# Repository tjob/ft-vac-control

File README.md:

# Use a Festool Bluetooth remote control with any vacuum

Use the Festool Bluetooth remote with vacuum extractors from other manufacturers.

The project contains the schematics and PCB layout designed using [KiCad 7](https://www.kicad.org/), and the firmware (written in C) for the [Raspberry Pi Pico](https://www.raspberrypi.com/products/raspberry-pi-pico/) to interface with a [Festool No. 202097 Bluetooth Remote Control add-on](https://www.amazon.co.uk/Festool-202097-Remote-Control-Blue/dp/B0794ZWFLR).

Festool sell an upgrade for their CT26/36/48 vacuum extractors to give remote control using Bluetooth, CT-F I/M-Set. It has two parts: the "CT-F I/M" installs in the extractor and the "CT-F I" is the button that attaches to the end of the vacuum hose. The button then starts and stops the extractor. Paired cordless tools with their Bluetooth-enabled batteries can also control the extractor.

But I don't have a CT26/36/48 extractor from Festool, so I wanted to create an adaptor that uses the module and controls a standard power socket to control any device attached. With a custom PCB, a Raspberry Pi Pico, some firmware, a Solid State Relay, and an enclosure I had a working solution.  Along the way I had to reverse-engineer the non-standard serial protocol and try to make sense of the bytes sent.

## Features
 - Allows connecting any vacuum extractor that has a physical switch capable of being always on. A vacuum with an NVR will not work.
 - Works with an unmodified Festool No. 202097 receiver. It's Plug and Play. At a later date if I ever get a CT extractor I wanted to be able to use this module again.
 - Has software safety features: automatically turns off if left on for an extended period. Uses the RP2040's hardware watchdog to shut off the power if the software stops for any reason.
 - Should work with Festool cordless tools with their Bluetooth batteries (untested). 

## How it works
The Festool module has three electrical connections to the host vacuum: two for power and one for data. The data line is serial, probably bidirectional, and uses a form of Manchester encoding. For more details on the serial stream and commands, see the [description of the traces](./software/traces/) captured with a logic analyzer.

The serial data from the receiver feeds the Raspberry Pi Pico via a BSS138 MOSFET as a level shifter. The Pico decodes the Manchester-encoded stream. When the Start/Stop commands are seen the software switches a Solid State Relay controlling mains AC supply to the output socket.

Wanting an excuse to learn KiCad, I designed a custom PCB to host the Pi Pico and a 4-pin 3.96 mm header to plug the CT-F I/M Bluetooth module into. The board contains a 240V switch-mode regulator providing 5V DC power to both the Pico and the CT-F I/M.

## :zap: Mains voltage electricity can kill! :zap: 

> [!WARNING] 
> This project description is not a guide and does not detail how to assemble a unit safely.  If you are not sure how to build one that is safe and complies with local laws and regulations, DO NOT ATTEMPT TO RECREATE.

## Bill of Materials

Parts on the PCB
| Part | Reference Designator | Description |
| ---- | -------------------- | ----------- |
| MCU | U1 | Raspberry Pi Pico, [the cheap one](https://thepihut.com/products/raspberry-pi-pico?variant=41925332533443)|
| 5V PCB mount PSU | PS1 | [Vigortronix VTX-214-005-005 5W Miniature SMPS AC-DC Converter 5V Output](https://www.rapidonline.com/vigortronix-vtx-214-005-005-5w-miniature-smps-ac-dc-converter-5v-output-84-2731) |
| Fuse holder | F1 | [5.2x20mm PCB Fuse Holder W/Cover 6.3A 250VAC](https://www.switchelectronics.co.uk/products/5-2x20mm-pcb-fuse-holder-w-cover-6-3a-250vac) |
| PSU protection diode | D1 | Optional, diode to stop power from USB flowing back into the PSU. If not installed, bridge JP2 instead |
| RX data port | J1 | Connects to the Festool receiver module. 4 pin, 3.96mm pitch header with plastic tab cut off - e.g. [JST B4P-VH(LF)(SN)](https://www.rapidonline.com/jst-b4p-vh-lf-sn-4-pole-top-entry-vh-series-p3-96-mm-22-5294) |
| SSR driver header | J2 | 2 way, 2.54mm board-to-wire header for connecting to the input of the SSR |
| Wago 3 way PCB connector | J5, J6 |Wago part number 2604-1103 |
| Wago 4 way PCB connector | J7 | Wago part number 2604-1104 |
| Signal MOSFETs | Q1,  Q2| BSS138, in SOT-23 package |
| 10k Resistors | R1, R2, R3 | SMT 1206 package  |
| 4.7uH | L1 | Inductor, [RLB0913-4R7K](https://uk.farnell.com/bourns/rlb0913-4r7k/inductor-4-7uh-4a-10-radial/dp/2725243) |
| 100nF | C2, C4, C6, C7 | Decoupling capacitors, through-hole, 2.5mm pitch | 
| 470uF 10V | C1 | [Suntan TS13DJ1A471MSB040R 470uf 10V Low Imp Electrolytic Capacitor](https://www.rapidonline.com/suntan-ts13dj1a471msb040r-470uf-10v-low-imp-electrolytic-capacitor-11-3664) |
| X2 Capacitor | X2-Cap1 | [Vishay BFC2-336-20224 220n 275V X2 Suppression Capacitor](https://www.rapidonline.com/vishay-bfc2-336-20224-220n-275v-x2-suppression-capacitor-10-2680)|
| Debug UART | J4 |  Optional (usefully only for firmware development) |
| Test points | TP1, TP2 | Optional, do not populate |
| Aux port | J3 | Optional and currently unused |
| Reset switch | SW1 | Optional (usefully only for firmware development) |

Other mechanical and electrical parts 

| Parts | Count | Description |
| ----- | ----- | ----------- |
| Enclosure | 1 | 190mm x 190mm x 67mm die-cast aluminum box  |
| Mains plug + inlet cable | 1 | I used a molded plug on a cable cut from an IEC lead |
| Power in strain relief | 1 | Cable Gland M16 10mm - e.g. [50616PA7001SET](https://cpc.farnell.com/hylec/50616pa7001set/nylon-m16-cable-gland-grey/dp/CBBR4095) |
| Output socket | 1 | 13A Circular Panel Mount Socket Outlet, 13A - e.g. [735WHI](https://cpc.farnell.com/mk/735whi/1-gang-outlet-panel-mount/dp/PL00703)
| Green indicator | 1 | Panel mount, 22.5mm, 220-240v, to show if the incoming power is on - e.g. [LEDTECGREEN230VAC](https://www.rapidonline.com/techna-ledtecgreen230vac-led-pilot-light-green-220-240vac-28-5357) |
| Yellow indicator | 1 | Panel mount, 22.5mm, 220-240v, LED lamp, to show if the vacuum power is on - e.g. [LEDTECYELLOW230VAC](https://www.rapidonline.com/techna-ledtecyellow230vac-led-pilot-light-yellow-amber-220-240vac-28-5369) |
|PCB standoffs | 5 | M4 - length dependent on the enclosure used |
| M6 x 35mm cap screws | 2 | Black, for securing the Festool receiver module |
| Custom M6 standoffs | 2 | To receive the M6 screws from the Festool receiver module. Length depends on the enclosure used, 39.1mm was correct for me |
| PCB screws | 5 | M4 x 8mm |
| SSR | 1 | Random on Solid State Relay, must be switchable by 5V DC - e.g. [i-Autoc Panel Mount Solid State Relay, 25 A Max. Load, 280V AC](https://uk.rs-online.com/web/p/solid-state-relays/1640576) |
| SSR cover | 1 | [i-Autoc Kudom KPC-0A Solid State Relay Accessory Protective Cover Single Phase](https://www.rapidonline.com/i-autoc-kudom-kpc-0a-solid-state-relay-accessory-protective-cover-single-phase-60-1586) |
| SSR thermal pad | 1 |[i-Autoc Kudom KTP-0A Solid State Relay Accessory Thermal Pad KSI/KSJ](https://www.rapidonline.com/i-autoc-kudom-ktp-0a-solid-state-relay-accessory-thermal-pad-ksi-ksj-60-1587) |
| Mains wiring loom | Assorted | Line, Neutral, Earth (CPC), sided appropriately for your max load. I used stranded 2.5mm<sup>2</sup> |
| Bits 'n' Bobs | Assorted | Hardware to attach standoffs to enclosure and to mount the SSR, earth bonding nuts and bolds, and crimp eyelets and spade connectors |

## License
The software, schematic designs and PCB layout contained in this repository are released under the MIT license.

## Credits
I got the pinout for the Bluetooth receiver from YouTube channel "My Project Box". His video ["Festool Bluetooth Hack / Mod works with any dust extractor!"](https://www.youtube.com/watch?v=EyrakKOR5tI) shows a very neat solution with a different approach; avoiding any software.

On Github, user gilbertf published [libft](https://github.com/gilbertf/libft) capable of both sending and receiving. It's not used by this project but his encoder appears to send the same bytes my decoder expects, which gave me some confidence that the implementation here is somewhat interoperable.

I used the Pi Pico KiCAD symbol and footprint from [ncarandini/KiCad-RP-Pico](https://github.com/ncarandini/KiCad-RP-Pico)

## Other projects inspired by this one
This project helped [Loriowar](https://github.com/Loriowar) create a [Festool receiver handler](https://github.com/Loriowar/festool_ct-f_im_handler) for Arduino.

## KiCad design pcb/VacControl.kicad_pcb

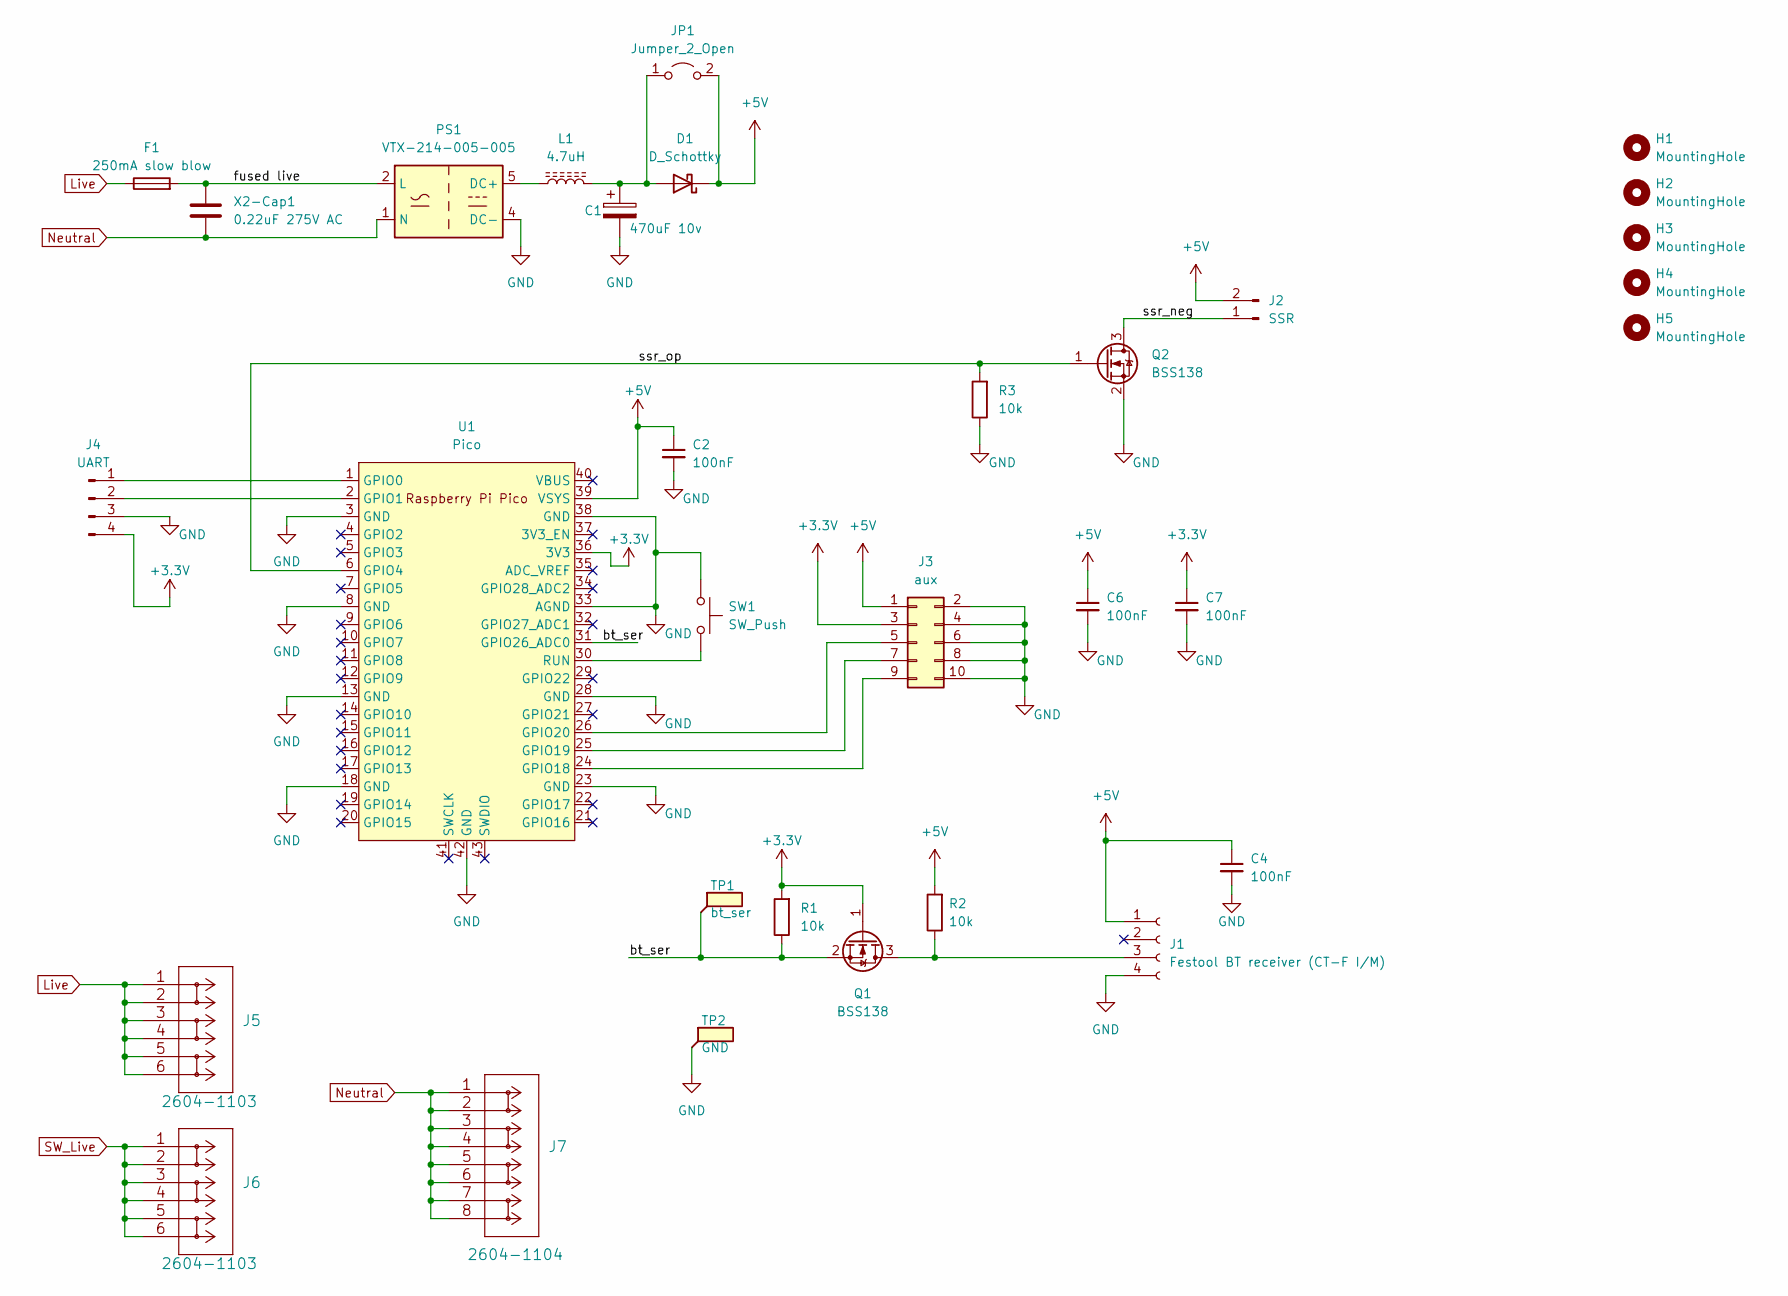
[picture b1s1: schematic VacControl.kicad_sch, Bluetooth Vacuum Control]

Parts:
C1: 470uF 10v; CP_Radial_D8.0mm_P3.50mm
C2, C4, C6, C7: 100nF; C_Rect_L4.6mm_W3.0mm_P2.50mm_MKS02_FKP02
D1: D_Schottky; D_SMC_Handsoldering
F1: 250mA slow blow; Fuseholder_Cylinder-5x20mm_Stelvio-Kontek_PTF78_Horizontal_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
H1, H2, H3, H4, H5: MountingHole; MountingHole_4.3mm_M4
J1: Festool BT receiver (CT-F I/M); BT receiver
J2: SSR; Molex_KK-254_AE-6410-02A_1x02_P2.54mm_Vertical
J3: aux; IDC-Header_2x05_P2.54mm_Vertical
J4: UART; PinSocket_1x04_P2.54mm_Vertical
J5, J6: 2604-1103
J7: 2604-1104
JP1: Jumper_2_Open; TestPoint_2Pads_Pitch2.54mm_Drill0.8mm
L1: 4.7uH; L_Radial_D7.8mm_P5.00mm_Fastron_07HCP
PS1: VTX-214-005-005; Converter_ACDC_Vigortronix_VTX-214-005-0xx_THT
Q1, Q2: BSS138; SOT-23_Handsoldering
R1, R2, R3: 10k; R_1206_3216Metric_Pad1.30x1.75mm_HandSolder
SW1: SW_Push; SW_PUSH_6mm_H4.3mm
TP1: bt_ser; Pin_D0.9mm_L10.0mm_W2.4mm_FlatFork
TP2: GND; Pin_D0.9mm_L10.0mm_W2.4mm_FlatFork
U1: Pico; RPi_Pico_SMD_TH
X2-Cap1: 0.22uF 275V AC; C_Rect_L18.0mm_W7.0mm_P15.00mm_FKS3_FKP3

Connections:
+3.3V: C7.1, J3.3, J4.4, Q1.1 (G), R1.2, U1.36 (3V3)
+5V: C2.1, C4.1, C6.1, D1.1 (K), J1.1, J2.2, J3.1, JP1.2 (B), R2.2, U1.39 (VSYS)
/bt_ser: Q1.2 (S), R1.1, TP1.1, U1.31 (GPIO26_ADC0)
/fused live: F1.2, PS1.2 (L), X2-Cap1.1
/ssr_neg: J2.1, Q2.3 (D)
/ssr_op: Q2.1 (G), R3.2, U1.6 (GPIO4)
GND: C1.2, C2.2, C4.2, C6.2, C7.2, J1.4, J3.2, J3.4, J3.6, J3.8, J3.10, J4.3, PS1.4 (DC-), Q2.2 (S), R3.1, SW1.1, TP2.1, U1.3 (GND), U1.8 (GND), U1.13 (GND), U1.18 (GND), U1.23 (GND), U1.28 (GND), U1.33 (AGND), U1.38 (GND), U1.42 (GND)
Live: F1.1, J5.1, J5.2, J5.3, J5.4, J5.5, J5.6
unnamed: C1.1, D1.2 (A), JP1.1 (A), L1.2
unnamed: J1.3, Q1.3 (D), R2.1
unnamed: J3.5, U1.26 (GPIO20)
unnamed: J3.7, U1.25 (GPIO19)
unnamed: J3.9, U1.24 (GPIO18)
unnamed: J4.1, U1.1 (GPIO0)
unnamed: J4.2, U1.2 (GPIO1)
unnamed: L1.1, PS1.5 (DC+)
unnamed: SW1.2, U1.30 (RUN)
Neutral: J7.1, J7.2, J7.3, J7.4, J7.5, J7.6, J7.7, J7.8, PS1.1 (N), X2-Cap1.2
SW_Live: J6.1, J6.2, J6.3, J6.4, J6.5, J6.6

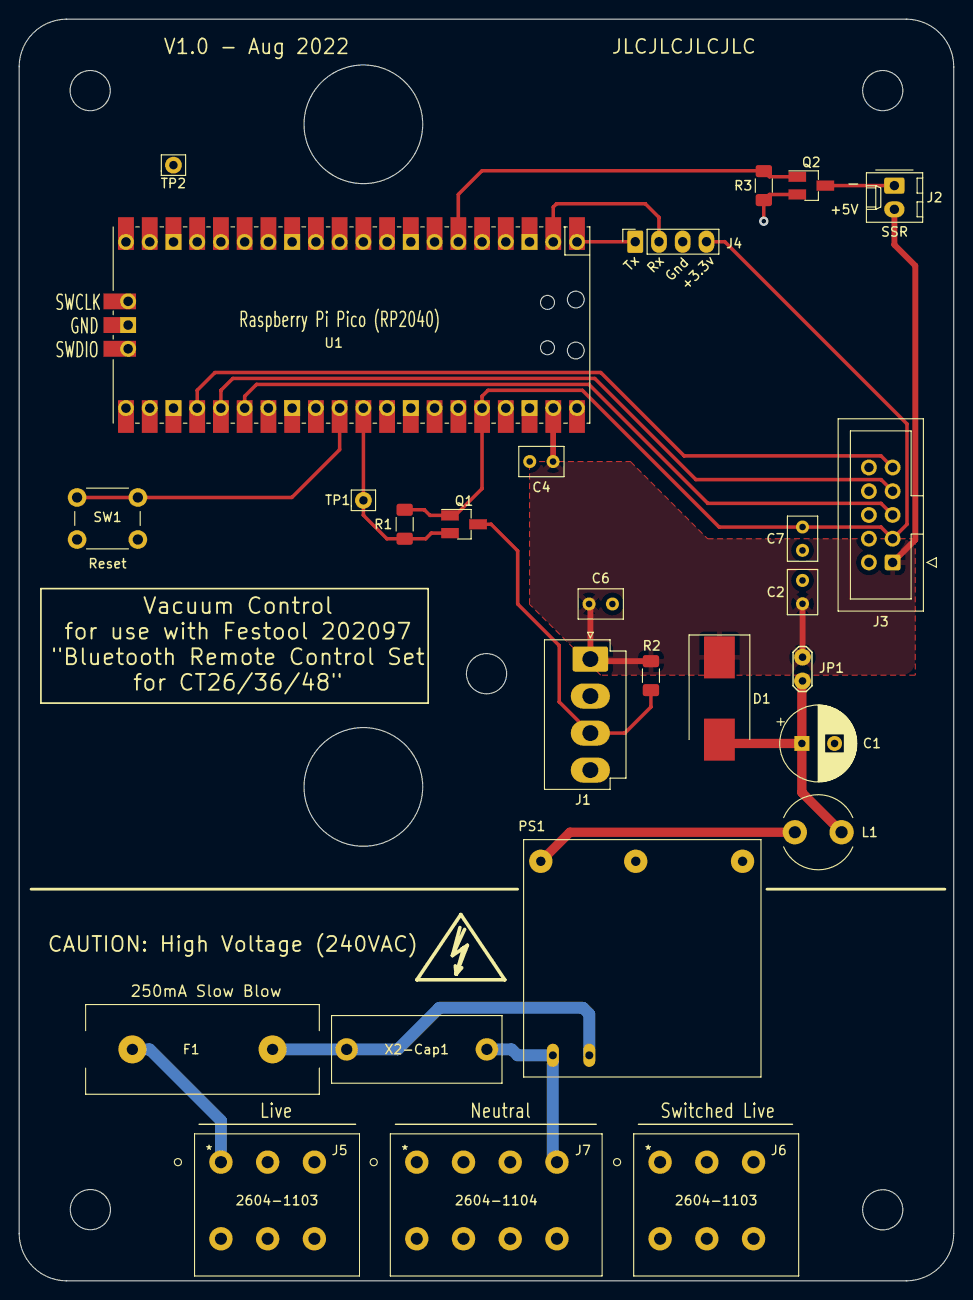
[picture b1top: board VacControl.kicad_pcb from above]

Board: 2 copper layers, 100.0 x 135.0 mm, 33 parts (0 on the bottom side), 19 nets.

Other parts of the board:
CAUTION: High Voltage (240VAC): Warning; Symbol_HighVoltage_Type2_CopperTop_VerySmall

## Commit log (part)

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2023-03-22 Basic decoder untested
2023-03-23 Build and workspace files
2023-04-01 - Specify the GPIO pin when initilizing the decoder. - It's chirp not chip.
2023-04-02 Bug fixes and start of safety. - Building up recived message was broken due to bad boolan logic. - Automaticaly turn off vacuum if left on for longer than 1 hour.
2023-04-02 Added hardware watchdog support and tidy up some magic numbers
2023-04-02 Documentation
2023-04-02 More documentation
2023-04-04 More documentation and trace files used to derive the decoder.
2023-04-04 cleanup
2023-04-04 Better description of messages in decoder
2023-04-04 Formating
2023-04-04 Better description of upper and lower chirp
2023-04-04 Compile with warnings as errors.
2023-04-05 More details on the traces and added pulse view workspaces to keep the timing decoders.
2023-04-05 typedef the structures. Store message length with the messages when queueing.
2023-04-06 Some images for the docs
2023-04-06 Continuing the documentation with the main project readme.
2023-04-06 KiCad 7 Schematic and PCB files
2023-04-06 Add missing PCB file
2023-04-07 More images
2023-04-07 Added referance image of the schematics and a license section to the readme
2023-04-07 Move the license to the root directory
2023-07-12 YouTube image for video link
2023-07-12 Added demo video from YouTube
2023-12-23 Pull in pico_sdk more directly as we have it as a git submodule
2024-06-08 Add more explanation of the decoder states.
2024-06-08 Cleanup main loop - Shorten the auto off duration. - Simplify the led proof-of-life blinker. - Reduce the latancy when a message is received over Blue Tooth.
2024-12-02 Added BOM and link to similar project
2024-12-02 Update README.md
    Fix markdown formatting.
2025-09-22 Minor spelling fixes and updates to README files
2025-11-09 Wavedrom svg with white backround so that it renders correclty with darkmode on.

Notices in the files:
parts and their libraries:
Copyright 2021 Accelerated Designs. All rights reserved.
